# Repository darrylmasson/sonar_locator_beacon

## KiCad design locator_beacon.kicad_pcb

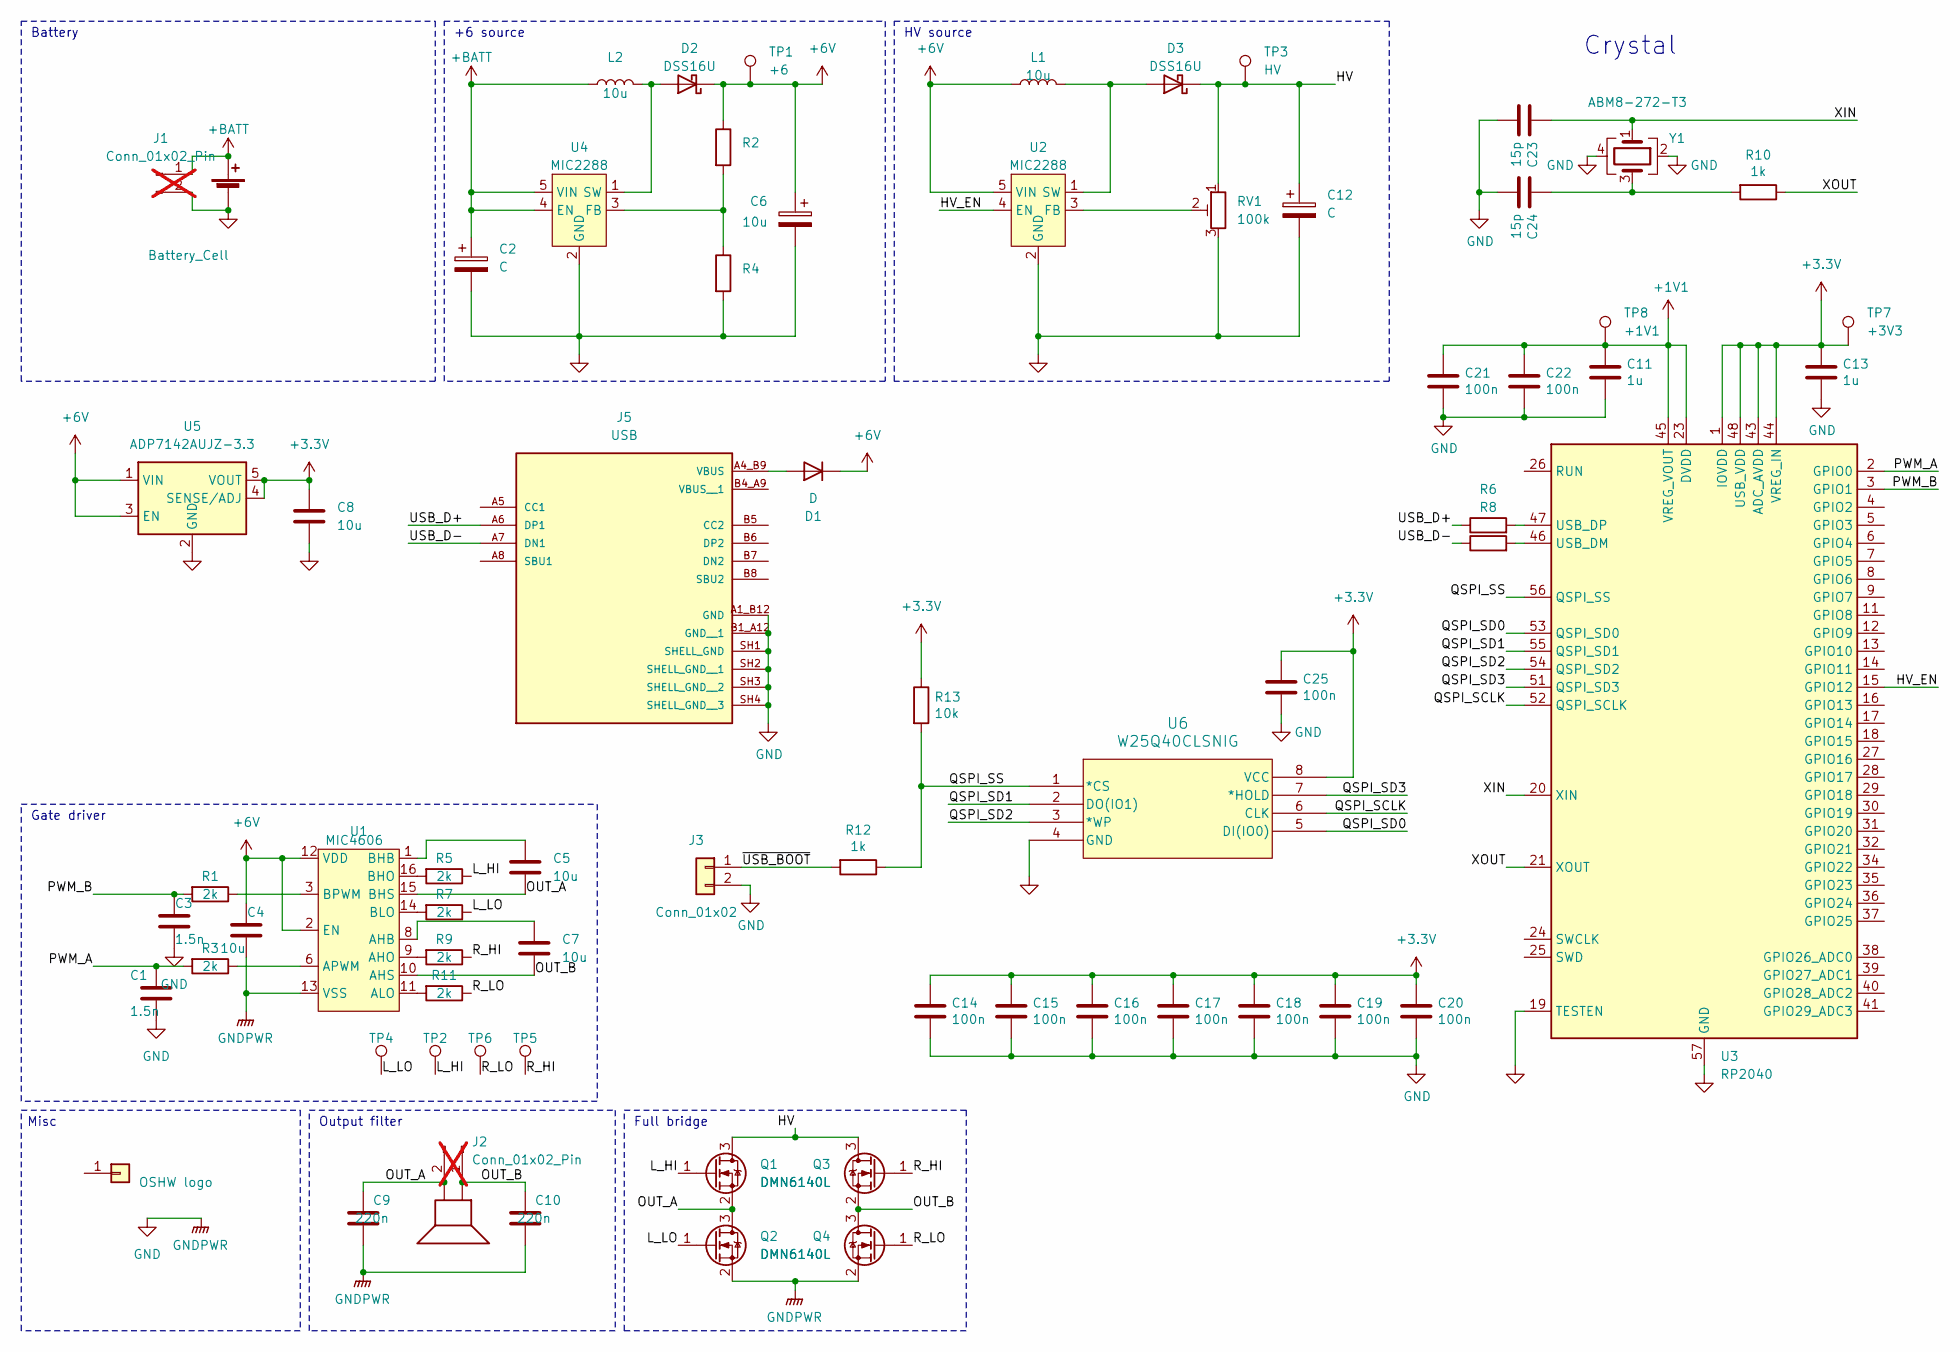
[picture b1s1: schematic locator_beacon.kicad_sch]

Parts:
BT1: Battery_Cell; PinHeader_1x02_P2.54mm_Vertical
C1, C3: 1.5n; C_0805_2012Metric
C2: C; C_0805_2012Metric
C4, C5, C7, C8: 10u; C_0805_2012Metric
C6: 10u; CP_Elec_4x3.9
C9, C10: 220n; C_0805_2012Metric
C11, C13: 1u; C_0402_1005Metric
C12: C; CP_Elec_4x3.9
C14, C15, C16, C17, C18, C19, C20, C21, C22, C25: 100n; C_0402_1005Metric
C23, C24: 15p; C_0402_1005Metric
D1: D; D_SOD-123
D2, D3: DSS16U; D_SOD-123
J1: Conn_01x02_Pin; PinSocket_1x02_P1.27mm_Vertical; not fitted
J2: Conn_01x02_Pin; PinHeader_1x02_P1.27mm_Vertical; not fitted
J3: Conn_01x02; PinHeader_1x02_P2.54mm_Vertical
J4: OSHW logo; OSHW-Logo_5.7x6mm_SilkScreen
J5: USB; GCT_USB4105-GF-A; PARTREV B3
L1, L2: 10u; C_0805_2012Metric
OUT1: Speaker; PinSocket_1x02_P2.54mm_Vertical
Q1, Q2, Q3, Q4: DMN6140L; SOT-23
R1, R3, R5, R7, R9, R11: 2k; R_0805_2012Metric
R2, R4: R_0805_2012Metric
R6, R8: R_0402_1005Metric
R10: 1k; R_0402_1005Metric
R12: 1k; R_0805_2012Metric
R13: 10k; R_0805_2012Metric
RV1: 100k; Potentiometer_Bourns_3314J_Vertical
TP1: +6; TestPoint_Pad_D1.0mm
TP2: LHI; TestPoint_Pad_D1.0mm
TP3: HV; TestPoint_Pad_D1.0mm
TP4: LLO; TestPoint_Pad_D1.0mm
TP5: RHI; TestPoint_Pad_D1.0mm
TP6: RLO; TestPoint_Pad_D1.0mm
TP7: +3V3; TestPoint_Pad_D1.0mm
TP8: +1V1; TestPoint_Pad_D1.0mm
U1: MIC4606; TSSOP-16-1EP_4.4x5mm_P0.65mm
U2, U4: MIC2288; TSOP-5_1.65x3.05mm_P0.95mm
U3: RP2040; QFN-56-1EP_7x7mm_P0.4mm_EP3.2x3.2mm
U5: ADP7142AUJZ-3.3; TSOT-23-5
U6: W25Q40CLSNIG; WIN_SN-8_WIN
Y1: ABM8-272-T3; Crystal_SMD_3225-4Pin_3.2x2.5mm

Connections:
+1V1: C11.1, C21.1, C22.1, TP8.1, U3.23 (DVDD), U3.45 (VREG_VOUT), U3.50 (DVDD)
+3.3V: C8.1, C13.1, C14.1, C15.1, C16.1, C17.1, C18.1, C19.1, C20.1, C25.1, R13.1, TP7.1, U3.1 (IOVDD), U3.10 (IOVDD), U3.22 (IOVDD), U3.33 (IOVDD), U3.42 (IOVDD), U3.43 (ADC_AVDD), U3.44 (VREG_IN), U3.48 (USB_VDD), U3.49 (IOVDD), U5.4 (SENSE/ADJ), U5.5 (VOUT), U6.8 (VCC)
+6V: C4.1, C6.1, D1.1 (K), D2.1 (K), L1.1, R2.1, TP1.1, U1.2 (EN), U1.12 (VDD), U2.5 (VIN), U5.1 (VIN), U5.3 (EN)
+BATT: BT1.1 (+), C2.1, J1.1, L2.1, U4.4 (EN), U4.5 (VIN)
/HV: C12.1, D3.1 (K), Q1.3 (D), Q3.3 (D), RV1.1, TP3.1
/HV_EN: U2.4 (EN), U3.15 (GPIO12)
/L_HI: Q1.1 (G), R5.1, TP2.1
/L_LO: Q2.1 (G), R7.1, TP4.1
/OUT_A: C5.2, C9.1, J2.2, OUT1.2, Q1.2 (S), Q2.3 (D), U1.15 (BHS)
/OUT_B: C7.2, C10.1, J2.1, OUT1.1, Q3.2 (S), Q4.3 (D), U1.10 (AHS)
/PWM_A: C1.1, R3.2, U3.2 (GPIO0)
/PWM_B: C3.1, R1.2, U3.3 (GPIO1)
/QSPI_SCLK: U3.52 (QSPI_SCLK), U6.6 (CLK)
/QSPI_SD0: U3.53 (QSPI_SD0), U6.5 (DI(IO0))
/QSPI_SD1: U3.55 (QSPI_SD1), U6.2 (DO(IO1))
/QSPI_SD2: U3.54 (QSPI_SD2), U6.3 (*WP)
/QSPI_SD3: U3.51 (QSPI_SD3), U6.7 (*HOLD)
/QSPI_SS: R12.1, R13.2, U3.56 (QSPI_SS), U6.1 (*CS)
/R_HI: Q3.1 (G), R9.1, TP5.1
/R_LO: Q4.1 (G), R11.1, TP6.1
/USB_D+: J5.A6 (DP1), R6.1
/USB_D-: J5.A7 (DN1), R8.1
/XIN: C23.1, U3.20 (XIN), Y1.1
/XOUT: R10.1, U3.21 (XOUT)
/~USB_BOOT: J3.1, R12.2
GND: BT1.2 (-), C1.2, C2.2, C3.2, C4.2, C6.2, C8.2, C9.2, C10.2, C11.2, C12.2, C13.2, C14.2, C15.2, C16.2, C17.2, C18.2, C19.2, C20.2, C21.2, C22.2, C23.2, C24.2, C25.2, J1.2, J3.2, J5.A1_B12 (GND), J5.B1_A12 (GND__1), J5.SH1 (SHELL_GND), J5.SH2 (SHELL_GND__1), J5.SH3 (SHELL_GND__2), J5.SH4 (SHELL_GND__3), Q2.2 (S), Q4.2 (S), R4.2, RV1.3, U1.13 (VSS), U2.2 (GND), U3.19 (TESTEN), U3.57 (GND), U4.2 (GND), U5.2 (GND), U6.4 (GND), Y1.2, Y1.4
unnamed: C24.1, R10.2, Y1.3
unnamed: D1.2 (A), J5.A4_B9 (VBUS)
unnamed: D2.2 (A), L2.2, U4.1 (SW)
unnamed: D3.2 (A), L1.2, U2.1 (SW)
unnamed: C7.1, U1.8 (AHB)
unnamed: R9.2, U1.9 (AHO)
unnamed: R11.2, U1.11 (ALO)
unnamed: R3.1, U1.6 (APWM)
unnamed: C5.1, U1.1 (BHB)
unnamed: R5.2, U1.16 (BHO)
unnamed: R7.2, U1.14 (BLO)
unnamed: R1.1, U1.3 (BPWM)
unnamed: RV1.2, U2.3 (FB)
unnamed: R8.2, U3.46 (USB_DM)
unnamed: R6.2, U3.47 (USB_DP)
unnamed: R2.2, R4.1, U4.3 (FB)

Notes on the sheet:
Misc
HV source
Battery
Output filter
Crystal
+6 source
Gate driver
Full bridge

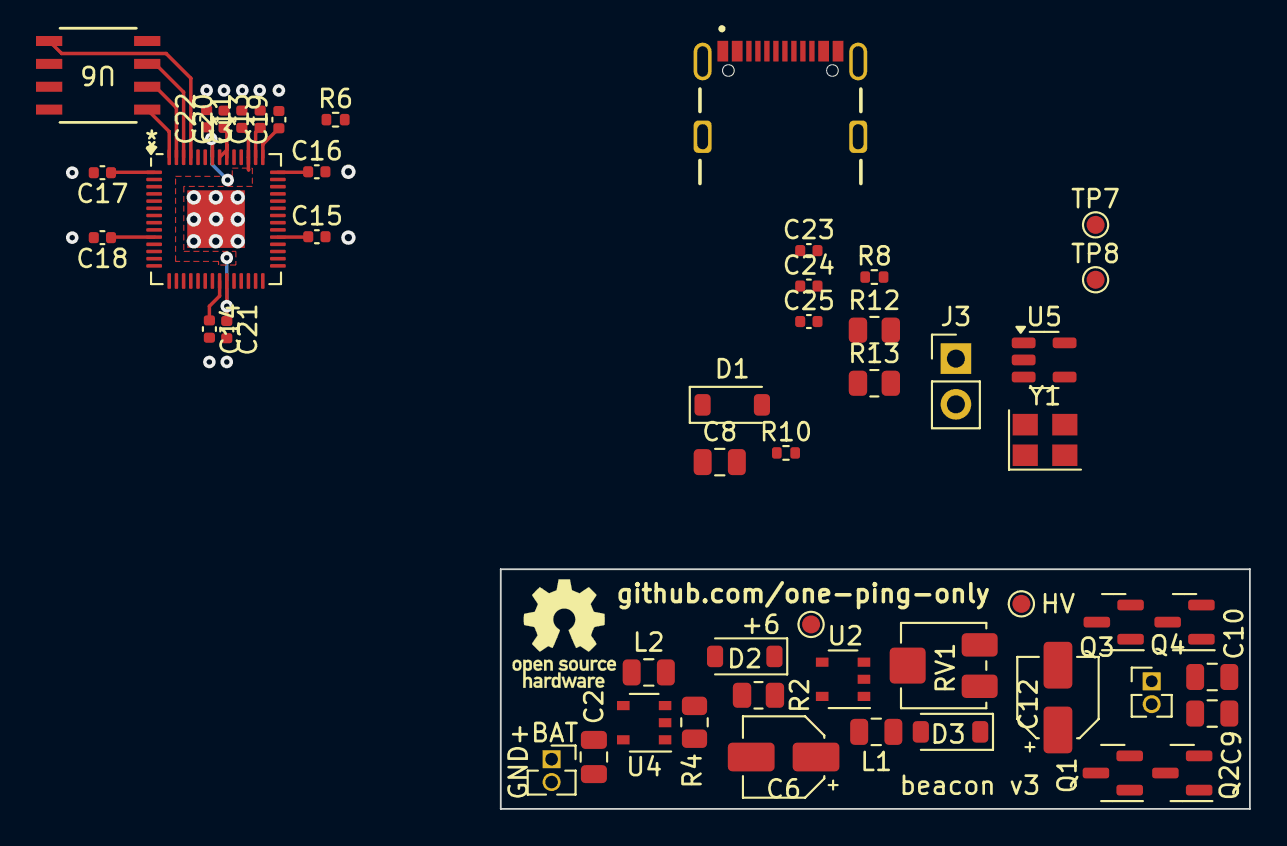
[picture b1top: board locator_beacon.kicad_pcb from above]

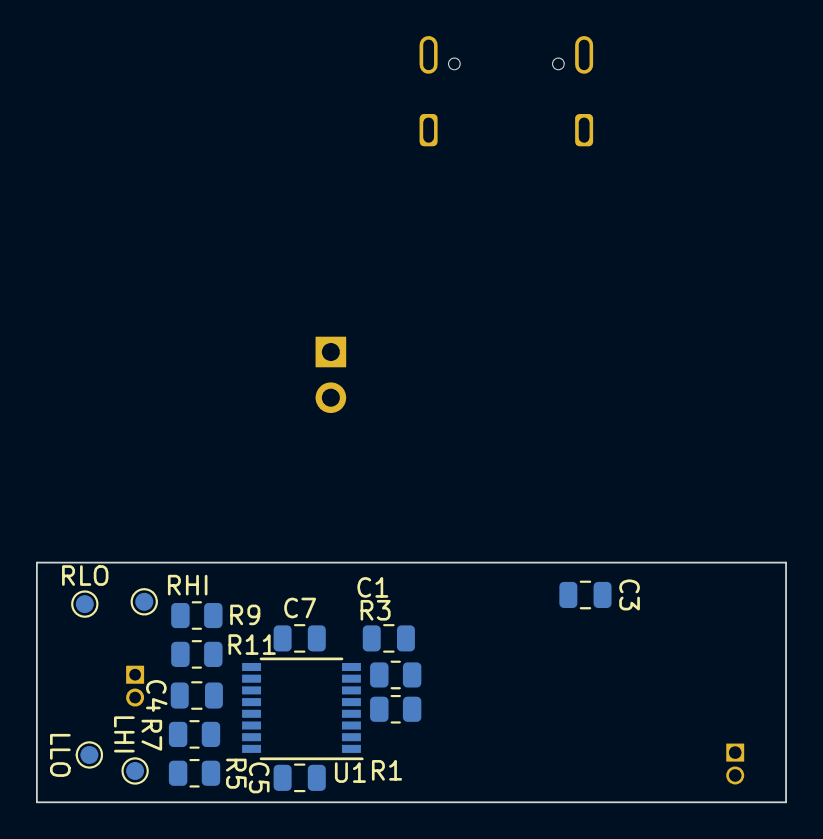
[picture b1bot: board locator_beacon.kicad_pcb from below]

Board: 2 copper layers, 41.6 x 13.3 mm, 68 parts (16 on the bottom side), 42 nets.

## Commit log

2024-04-26 555 driver
2024-05-09 Work
